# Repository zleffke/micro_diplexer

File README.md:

# micro_diplexer
KJ4QLP VHF/UHF Diplexer

## Credit where its due!
Inspired by the [KI0AG Micro-Duplexer](http://k0lee.com/duplexer.php) project.  I basically took this design and tweaked some of the values to modify the operating region of the diplexer.

### Note on Terminology - Diplexer vs. Duplexer
Both are three port devices.
A Diplexer is a devices that combines two separate bands (i.e VHF and UHF) into one port.  
A Duplexer is a device that combines two frequencies in the same band onto one port (like the input and output frequencies for a single band repeater).

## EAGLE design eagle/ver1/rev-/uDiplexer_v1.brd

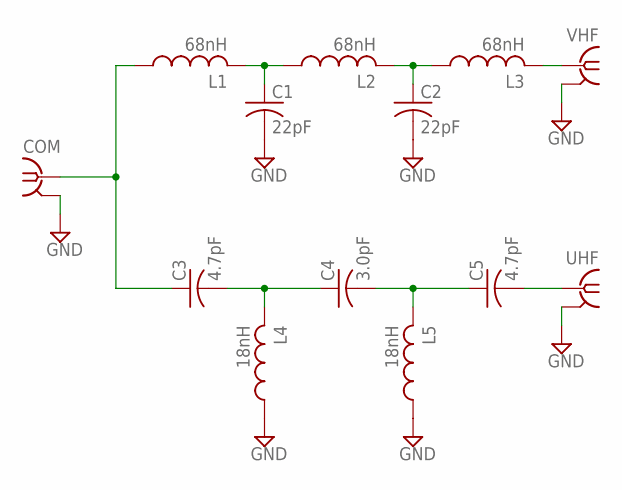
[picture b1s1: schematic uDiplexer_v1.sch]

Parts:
C1, C2: 22pF; C0805K
C3, C5: 4.7pF; C0805K
C4: 3.0pF; C0805K
COM: SMA-142-0711-821/826; J502-ND-142-0711-821/826
L1, L2, L3: 68nH; C0805K
L4, L5: 18nH; C0805K
UHF: SMA-142-0711-821/826; J502-ND-142-0711-821/826
VHF: SMA-142-0711-821/826; J502-ND-142-0711-821/826

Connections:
GND: C1.2, C2.2, COM.G@1 (2), COM.G@2 (2), COM.G@3 (2), COM.G@4 (2), L4.1, L5.1, UHF.G@1 (2), UHF.G@2 (2), UHF.G@3 (2), UHF.G@4 (2), VHF.G@1 (2), VHF.G@2 (2), VHF.G@3 (2), VHF.G@4 (2)
unnamed: C1.1, L1.2, L2.1
unnamed: C2.1, L2.2, L3.1
unnamed: L3.2, VHF.1
unnamed: C3.2, C4.1, L4.2
unnamed: C4.2, C5.1, L5.2
unnamed: C5.2, UHF.1
unnamed: C3.1, COM.1, L1.1

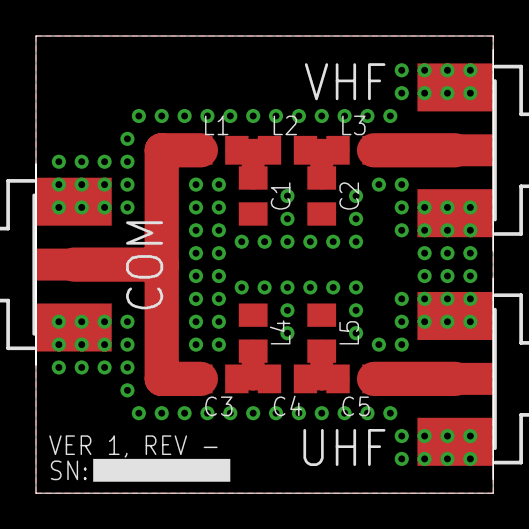
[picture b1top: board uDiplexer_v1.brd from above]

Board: 2 copper layers, 25.4 x 25.4 mm, 13 parts (0 on the bottom side), 8 nets.

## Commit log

2018-12-20 initial commit of qucs schematic and simulation. updated readme.
2018-12-20 added gitignore
2018-12-21 commit of two versions, PCB SMA and Edge Launch SMA. Ordered at Osh Park.
2018-12-21 adding BOM. Note the BOM has larger quantities than necessary (multiple builds, plus spares). It also has a few alternate values for experimentation.
